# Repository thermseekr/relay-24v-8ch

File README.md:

# RELAY-24V-8CH

Relay board with 8x 24 VDC 10A relays. This board is designed to be used togheter with [ESP-24V-16CH](https://github.com/thermseekr/esp-24v-16ch) and [ESP-24V-32CH](https://github.com/thermseekr/esp-24v-32ch), but can be driven by any 24V control circuit compatible with NPN inputs.

The dimensions are such that the board can be mounted on a PCB DIN rail holder from the Brazilian manufacturer Metaltex, check [here](https://www.metaltex.com.br/produtos/componentes/suportes/sp7-suporte-para-montagem-de-placa-de-circuito-impresso-em-trilho-din) for details.

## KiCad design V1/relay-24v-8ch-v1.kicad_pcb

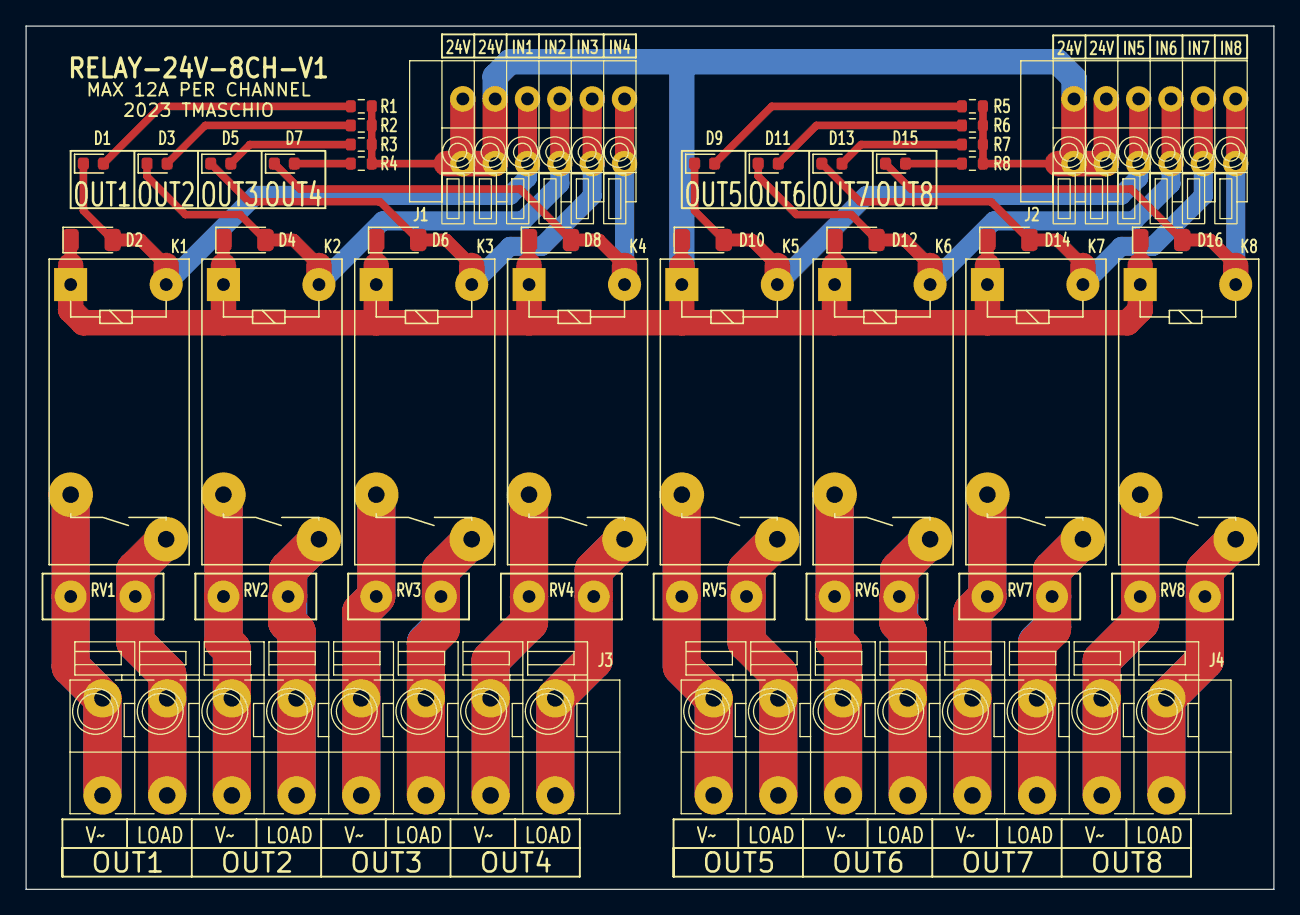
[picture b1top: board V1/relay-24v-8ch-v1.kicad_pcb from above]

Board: 2 copper layers, 98.0 x 67.8 mm, 44 parts (0 on the bottom side), 33 nets.

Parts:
D1, D3, D5, D7, D9, D11, D13, D15: GREEN; LED_0603_1608Metric
D2, D4, D6, D8, D10, D12, D14, D16: 1N4148; D_SOD-123
J1, J2: DB141V-2.54-6P; TerminalBlock_Dibo_DB141V-2.54-6P_1x06_P2.54mm_Vertical
J3, J4: DB142V-5.08-8P; TerminalBlock_Dibo_DB142V-5.08-8P_1x08_P5.08mm_Vertical
K1, K2, K3, K4, K5, K6, K7, K8: G5PZ-1A; Relay_SPST_Omron_G5PZ-1A
R1, R2, R3, R4, R5, R6, R7, R8: 5k6/100mW; R_0603_1608Metric
RV1, RV2, RV3, RV4, RV5, RV6, RV7, RV8: 275VAC; RV_Disc_D9.50mm_W3.6mm_P5.08mm

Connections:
+24V: D2.1 (K), D4.1 (K), D6.1 (K), D8.1 (K), D10.1 (K), D12.1 (K), D14.1 (K), D16.1 (K), J1.5, J1.6, J2.5, J2.6, K1.1, K2.1, K3.1, K4.1, K5.1, K6.1, K7.1, K8.1, R1.1, R2.1, R3.1, R4.1, R5.1, R6.1, R7.1, R8.1
unnamed: D1.2 (A), R1.2
unnamed: D1.1 (K), D2.2 (A), J1.4, K1.4
unnamed: D3.2 (A), R2.2
unnamed: D3.1 (K), D4.2 (A), J1.3, K2.4
unnamed: D5.2 (A), R3.2
unnamed: D5.1 (K), D6.2 (A), J1.2, K3.4
unnamed: D7.2 (A), R4.2
unnamed: D7.1 (K), D8.2 (A), J1.1, K4.4
unnamed: D9.2 (A), R5.2
unnamed: D9.1 (K), D10.2 (A), J2.4, K5.4
unnamed: D11.2 (A), R6.2
unnamed: D11.1 (K), D12.2 (A), J2.3, K6.4
unnamed: D13.2 (A), R7.2
unnamed: D13.1 (K), D14.2 (A), J2.2, K7.4
unnamed: D15.2 (A), R8.2
unnamed: D15.1 (K), D16.2 (A), J2.1, K8.4
unnamed: J3.1, K1.2, RV1.1
unnamed: J3.2, K1.3, RV1.2
unnamed: J3.3, K2.2, RV2.1
unnamed: J3.4, K2.3, RV2.2
unnamed: J3.5, K3.2, RV3.1
unnamed: J3.6, K3.3, RV3.2
unnamed: J3.7, K4.2, RV4.1
unnamed: J3.8, K4.3, RV4.2
unnamed: J4.1, K5.2, RV5.1
unnamed: J4.2, K5.3, RV5.2
unnamed: J4.3, K6.2, RV6.1
unnamed: J4.4, K6.3, RV6.2
unnamed: J4.5, K7.2, RV7.1
unnamed: J4.6, K7.3, RV7.2
unnamed: J4.7, K8.2, RV8.1
unnamed: J4.8, K8.3, RV8.2

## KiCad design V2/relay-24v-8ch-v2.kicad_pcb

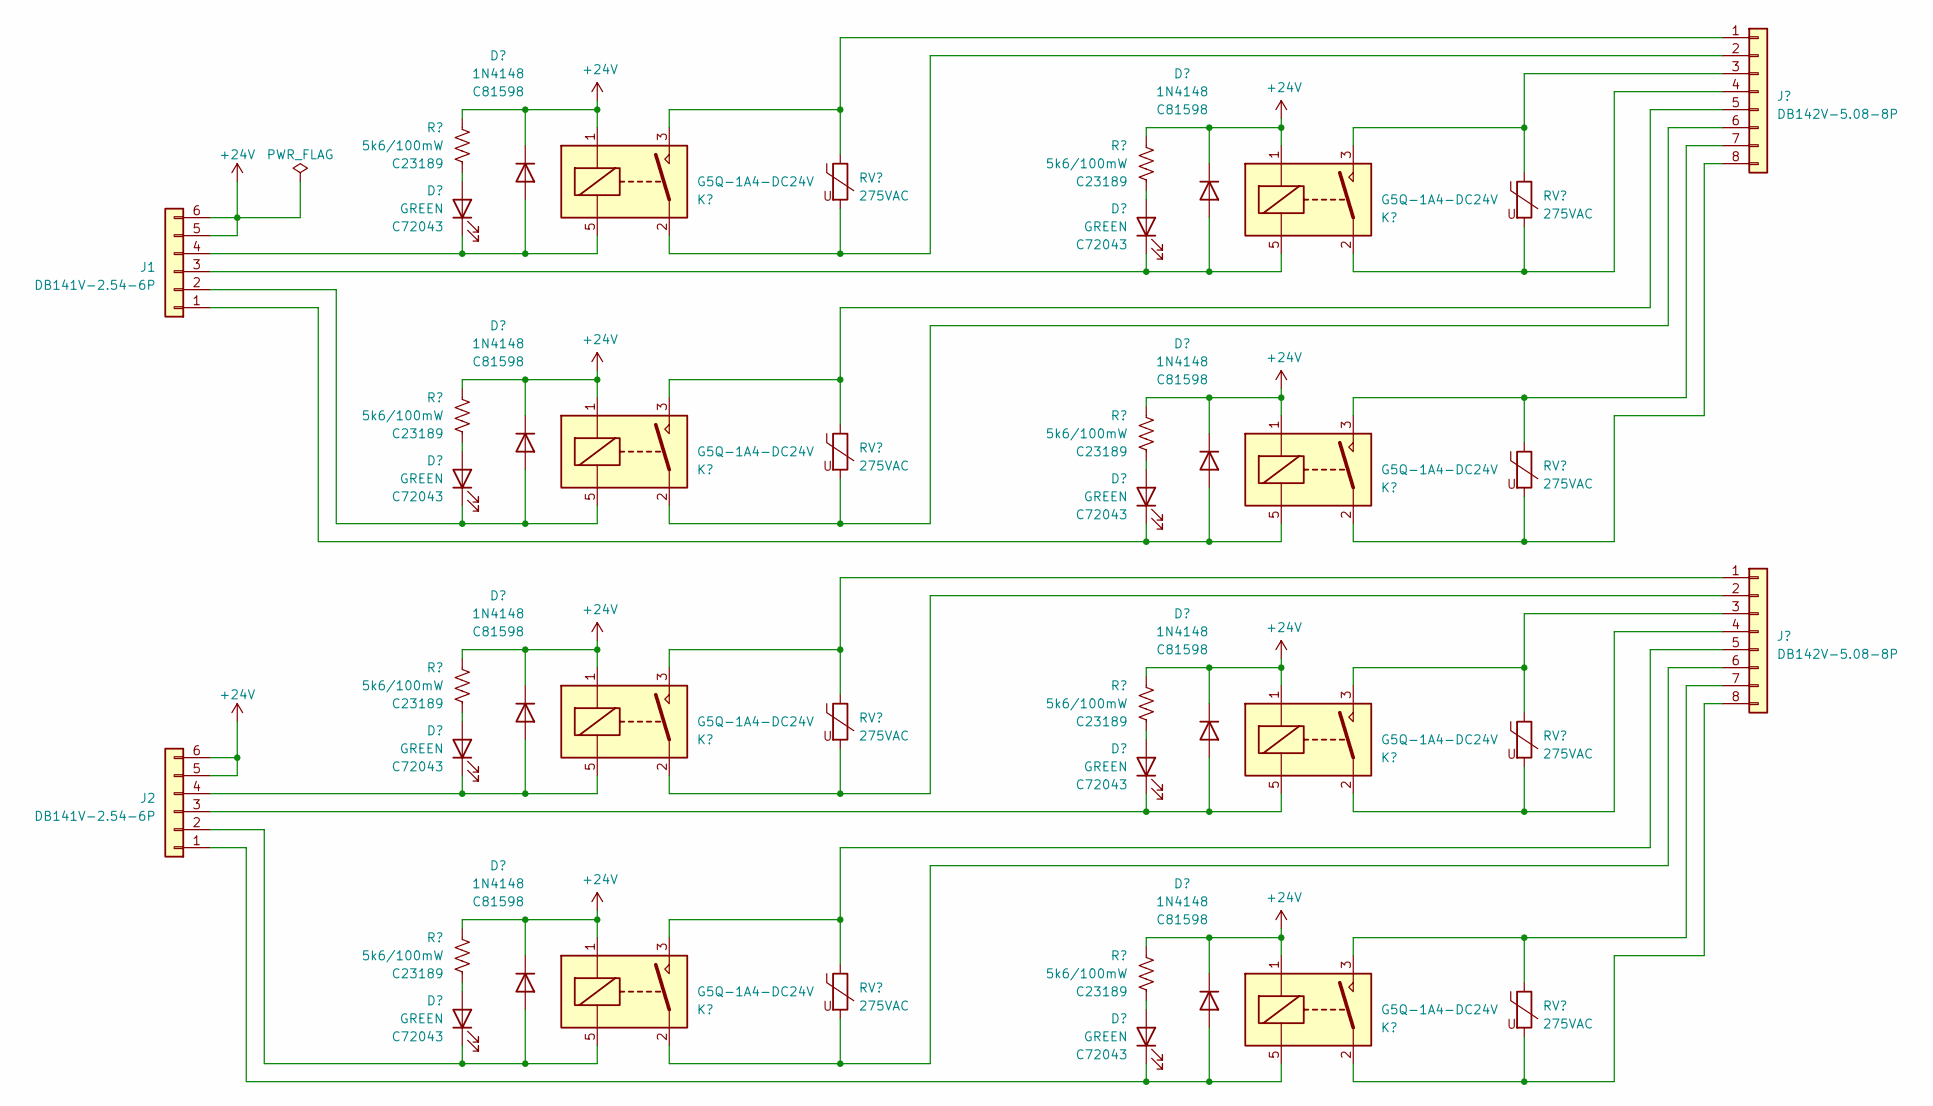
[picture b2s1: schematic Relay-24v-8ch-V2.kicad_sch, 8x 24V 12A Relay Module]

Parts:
D1, D3, D5, D7, D9, D11, D13, D15: GREEN; LED_0603_1608Metric; Mfr PN 19-217/GHC-YR1S2/3T; LCSC Part # C72043
D2, D4, D6, D8, D10, D12, D14, D16: 1N4148; D_SOD-123; Mfr PN 1N4148W; LCSC Part # C81598
J1, J2: DB141V-2.54-6P; TerminalBlock_Dibo_DB141V-2.54-6P_1x06_P2.54mm_Vertical; Mfr PN DB141V-2.54-6P; JLCPCB BOM 1
J3, J4: DB142V-5.08-8P; TerminalBlock_Dibo_DB142V-5.08-8P_1x08_P5.08mm_Vertical; Mfr PN DB142V-5.08-8P; JLCPCB BOM 1
K1, K2, K3, K4, K5, K6, K7, K8: G5Q-1A4-DC24V; Relay_SPST_Omron-G5Q-1A; Mfr PN G5Q-1A4-DC24V; JLCPCB BOM 1
R1, R2, R3, R4, R5, R6, R7, R8: 5k6/100mW; R_0603_1608Metric; Mfr PN 0603WAF5601T5E; LCSC Part # C23189
RV1, RV2, RV3, RV4, RV5, RV6, RV7, RV8: 275VAC; RV_Disc_D9.50mm_W3.6mm_P5.08mm; Mfr PN RM07D431KC1IE100; JLCPCB BOM 1

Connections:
+24V: D2.1 (K), D4.1 (K), D6.1 (K), D8.1 (K), D10.1 (K), D12.1 (K), D14.1 (K), D16.1 (K), J1.5, J1.6, J2.5, J2.6, K1.1, K2.1, K3.1, K4.1, K5.1, K6.1, K7.1, K8.1, R1.1, R2.1, R3.1, R4.1, R5.1, R6.1, R7.1, R8.1
unnamed: D1.2 (A), R1.2
unnamed: D1.1 (K), D2.2 (A), J1.4, K1.5
unnamed: D3.2 (A), R2.2
unnamed: D3.1 (K), D4.2 (A), J1.3, K2.5
unnamed: D5.2 (A), R3.2
unnamed: D5.1 (K), D6.2 (A), J1.2, K3.5
unnamed: D7.2 (A), R4.2
unnamed: D7.1 (K), D8.2 (A), J1.1, K4.5
unnamed: D9.2 (A), R5.2
unnamed: D9.1 (K), D10.2 (A), J2.4, K5.5
unnamed: D11.2 (A), R6.2
unnamed: D11.1 (K), D12.2 (A), J2.3, K6.5
unnamed: D13.2 (A), R7.2
unnamed: D13.1 (K), D14.2 (A), J2.2, K7.5
unnamed: D15.2 (A), R8.2
unnamed: D15.1 (K), D16.2 (A), J2.1, K8.5
unnamed: J3.1, K1.3, RV1.1
unnamed: J3.2, K1.2, RV1.2
unnamed: J3.3, K2.3, RV2.1
unnamed: J3.4, K2.2, RV2.2
unnamed: J3.5, K3.3, RV3.1
unnamed: J3.6, K3.2, RV3.2
unnamed: J3.7, K4.3, RV4.1
unnamed: J3.8, K4.2, RV4.2
unnamed: J4.1, K5.3, RV5.1
unnamed: J4.2, K5.2, RV5.2
unnamed: J4.3, K6.3, RV6.1
unnamed: J4.4, K6.2, RV6.2
unnamed: J4.5, K7.3, RV7.1
unnamed: J4.6, K7.2, RV7.2
unnamed: J4.7, K8.3, RV8.1
unnamed: J4.8, K8.2, RV8.2

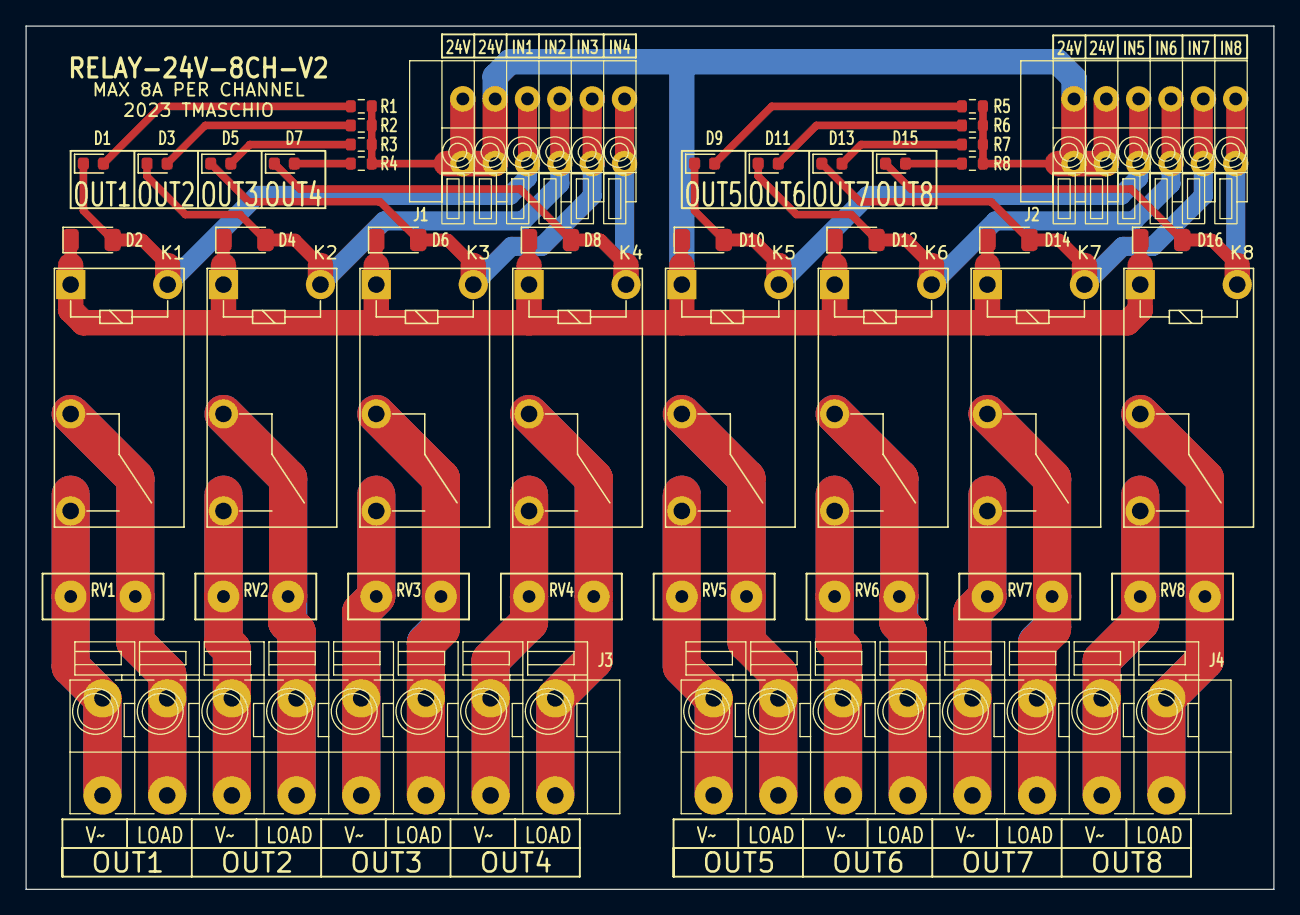
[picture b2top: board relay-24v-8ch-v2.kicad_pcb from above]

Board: 2 copper layers, 98.0 x 67.8 mm, 44 parts (0 on the bottom side), 33 nets.

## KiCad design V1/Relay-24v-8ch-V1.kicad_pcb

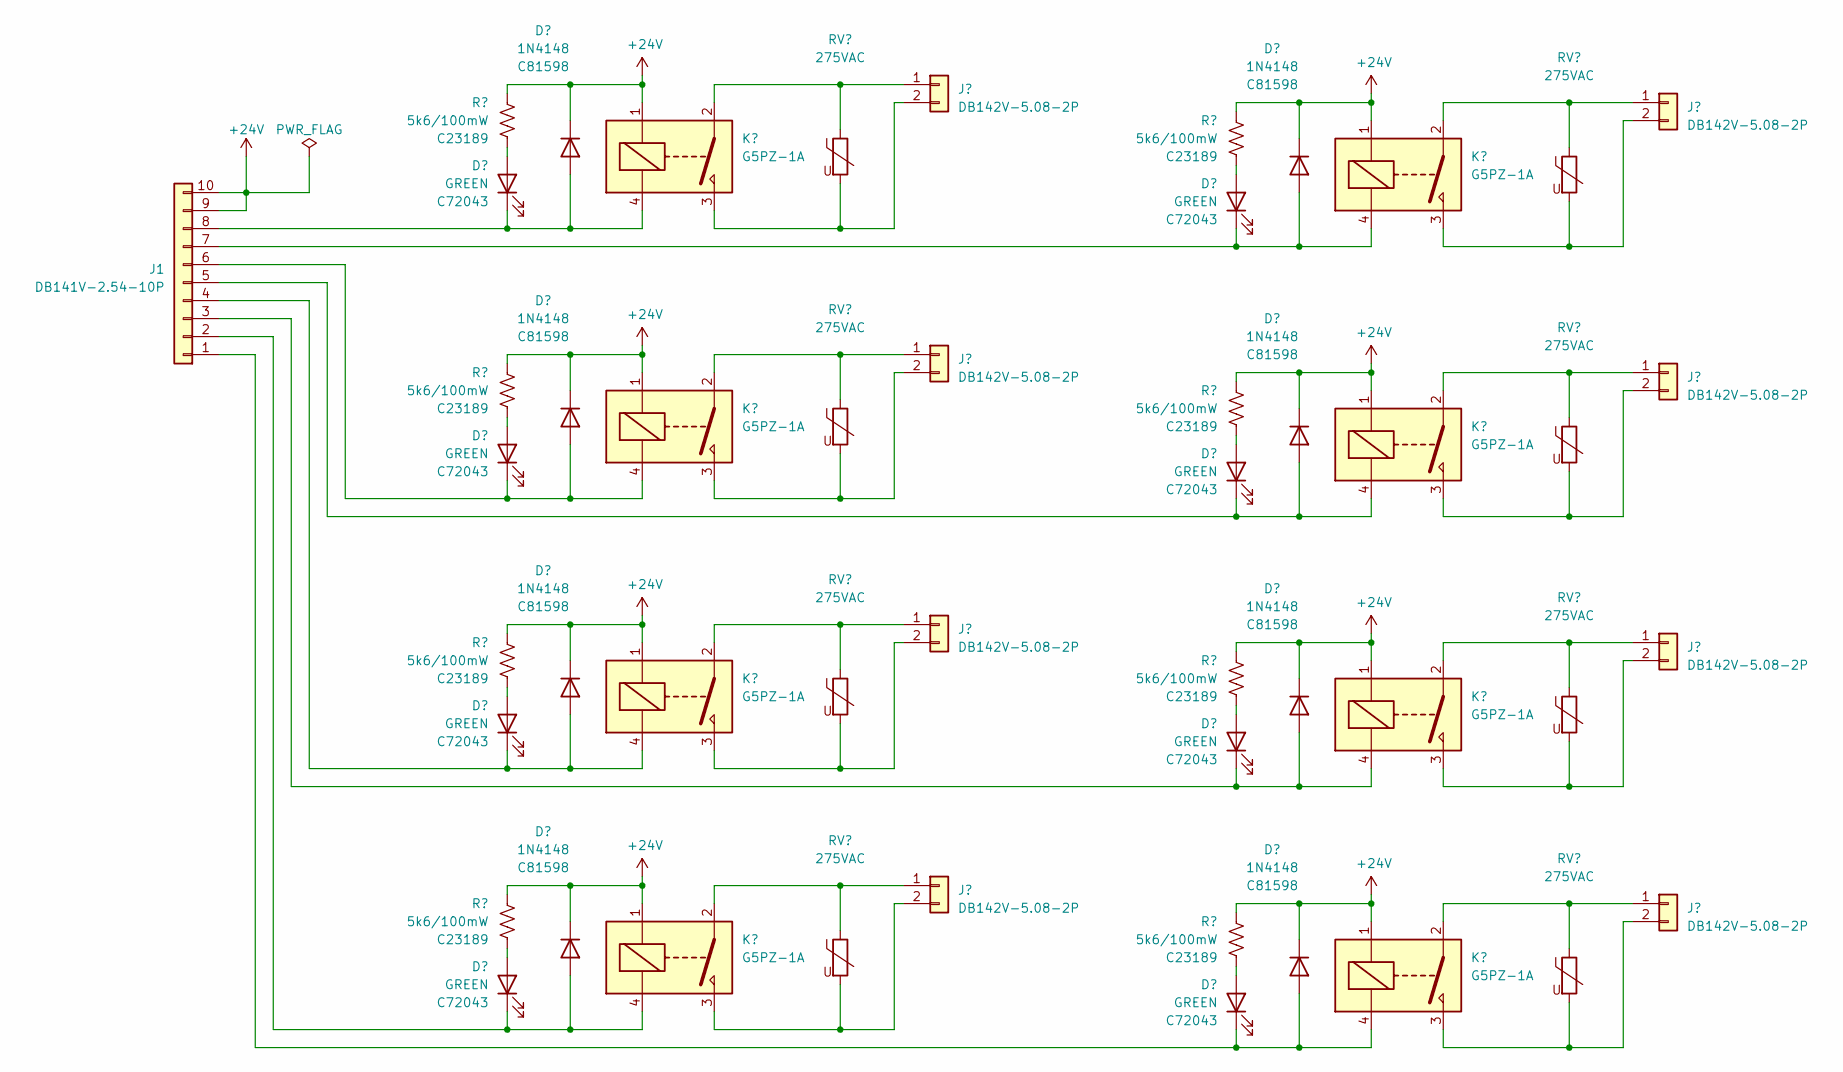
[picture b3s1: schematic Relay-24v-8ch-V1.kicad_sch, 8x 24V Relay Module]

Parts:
D1, D3, D5, D7, D9, D11, D13, D15: GREEN; LED_0603_1608Metric; Mfr PN 19-217/GHC-YR1S2/3T; LCSC Part # C72043
D2, D4, D6, D8, D10, D12, D14, D16: 1N4148; D_SOD-123; Mfr PN 1N4148W; LCSC Part # C81598
J1: DB141V-2.54-10P; TerminalBlock_Dibo_DB141V-2.54-10P_1x10_P2.54mm_Vertical; Mfr PN DB141V-2.54-10P; JLCPCB BOM 1
J2, J3, J4, J5, J6, J7, J8, J9: DB142V-5.08-2P; TerminalBlock_Dibo_DB142V-5.08-2P_1x02_P5.08mm_Vertical; Mfr PN DB142V-5.08-2P; JLCPCB BOM 1
K1, K2, K3, K4, K5, K6, K7, K8: G5PZ-1A; Relay_SPST_Omron_G5PZ-1A; Mfr PN G5PZ-1A; JLCPCB BOM 0
R1, R2, R3, R4, R5, R6, R7, R8: 5k6/100mW; R_0603_1608Metric; Mfr PN 0603WAF5601T5E; LCSC Part # C23189
RV1, RV2, RV3, RV4, RV5, RV6, RV7, RV8: 275VAC; RV_Disc_D9.50mm_W3.6mm_P5.08mm; Mfr PN RM07D431KC1IE100; JLCPCB BOM 1

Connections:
+24V: D2.1 (K), D4.1 (K), D6.1 (K), D8.1 (K), D10.1 (K), D12.1 (K), D14.1 (K), D16.1 (K), J1.9, J1.10, K1.1, K2.1, K3.1, K4.1, K5.1, K6.1, K7.1, K8.1, R1.1, R2.1, R3.1, R4.1, R5.1, R6.1, R7.1, R8.1
unnamed: D1.2 (A), R1.2
unnamed: D1.1 (K), D2.2 (A), J1.8, K1.4
unnamed: D3.2 (A), R2.2
unnamed: D3.1 (K), D4.2 (A), J1.7, K2.4
unnamed: D5.2 (A), R3.2
unnamed: D5.1 (K), D6.2 (A), J1.6, K3.4
unnamed: D7.2 (A), R4.2
unnamed: D7.1 (K), D8.2 (A), J1.5, K4.4
unnamed: D9.2 (A), R5.2
unnamed: D9.1 (K), D10.2 (A), J1.4, K5.4
unnamed: D11.2 (A), R6.2
unnamed: D11.1 (K), D12.2 (A), J1.3, K6.4
unnamed: D13.2 (A), R7.2
unnamed: D13.1 (K), D14.2 (A), J1.2, K7.4
unnamed: D15.2 (A), R8.2
unnamed: D15.1 (K), D16.2 (A), J1.1, K8.4
unnamed: J2.1, K1.2, RV1.1
unnamed: J2.2, K1.3, RV1.2
unnamed: J3.1, K2.2, RV2.1
unnamed: J3.2, K2.3, RV2.2
unnamed: J4.1, K3.2, RV3.1
unnamed: J4.2, K3.3, RV3.2
unnamed: J5.1, K4.2, RV4.1
unnamed: J5.2, K4.3, RV4.2
unnamed: J6.1, K5.2, RV5.1
unnamed: J6.2, K5.3, RV5.2
unnamed: J7.1, K6.2, RV6.1
unnamed: J7.2, K6.3, RV6.2
unnamed: J8.1, K7.2, RV7.1
unnamed: J8.2, K7.3, RV7.2
unnamed: J9.1, K8.2, RV8.1
unnamed: J9.2, K8.3, RV8.2

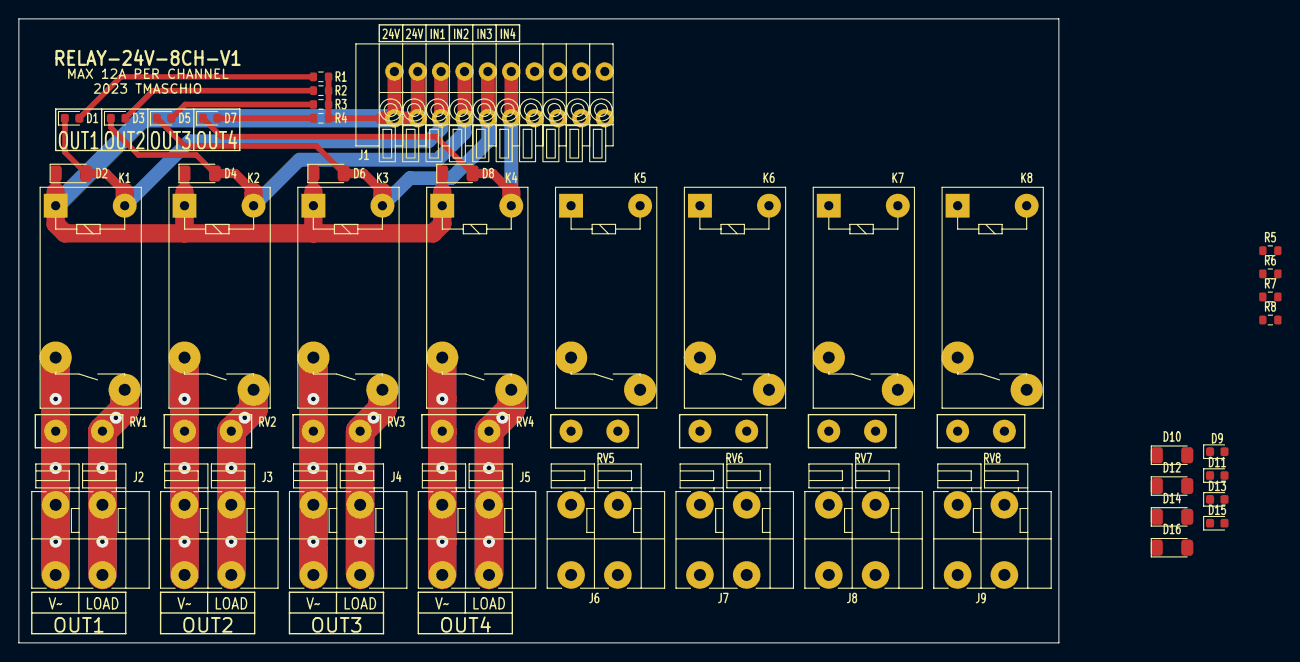
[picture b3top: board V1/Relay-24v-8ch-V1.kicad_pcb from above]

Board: 2 copper layers, 113.0 x 67.8 mm, 49 parts (0 on the bottom side), 33 nets.

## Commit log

2023-05-21 Change connector 3D model
2023-05-21 Update silkscreen and board image.
2023-05-22 Update to silkscreen and board image.
2023-05-22 Update board images
2023-05-22 Updates for fabrication
2023-05-23 Adjustments for fabrication
2023-08-21 Repository reorg and cleanup
2023-08-31 Varistor updated
2023-09-04 Cleanup
2023-09-04 Redone everything
2023-09-04 New board image
2023-09-06 Rename to lowercase
2024-10-02 Update to Kicad 8
